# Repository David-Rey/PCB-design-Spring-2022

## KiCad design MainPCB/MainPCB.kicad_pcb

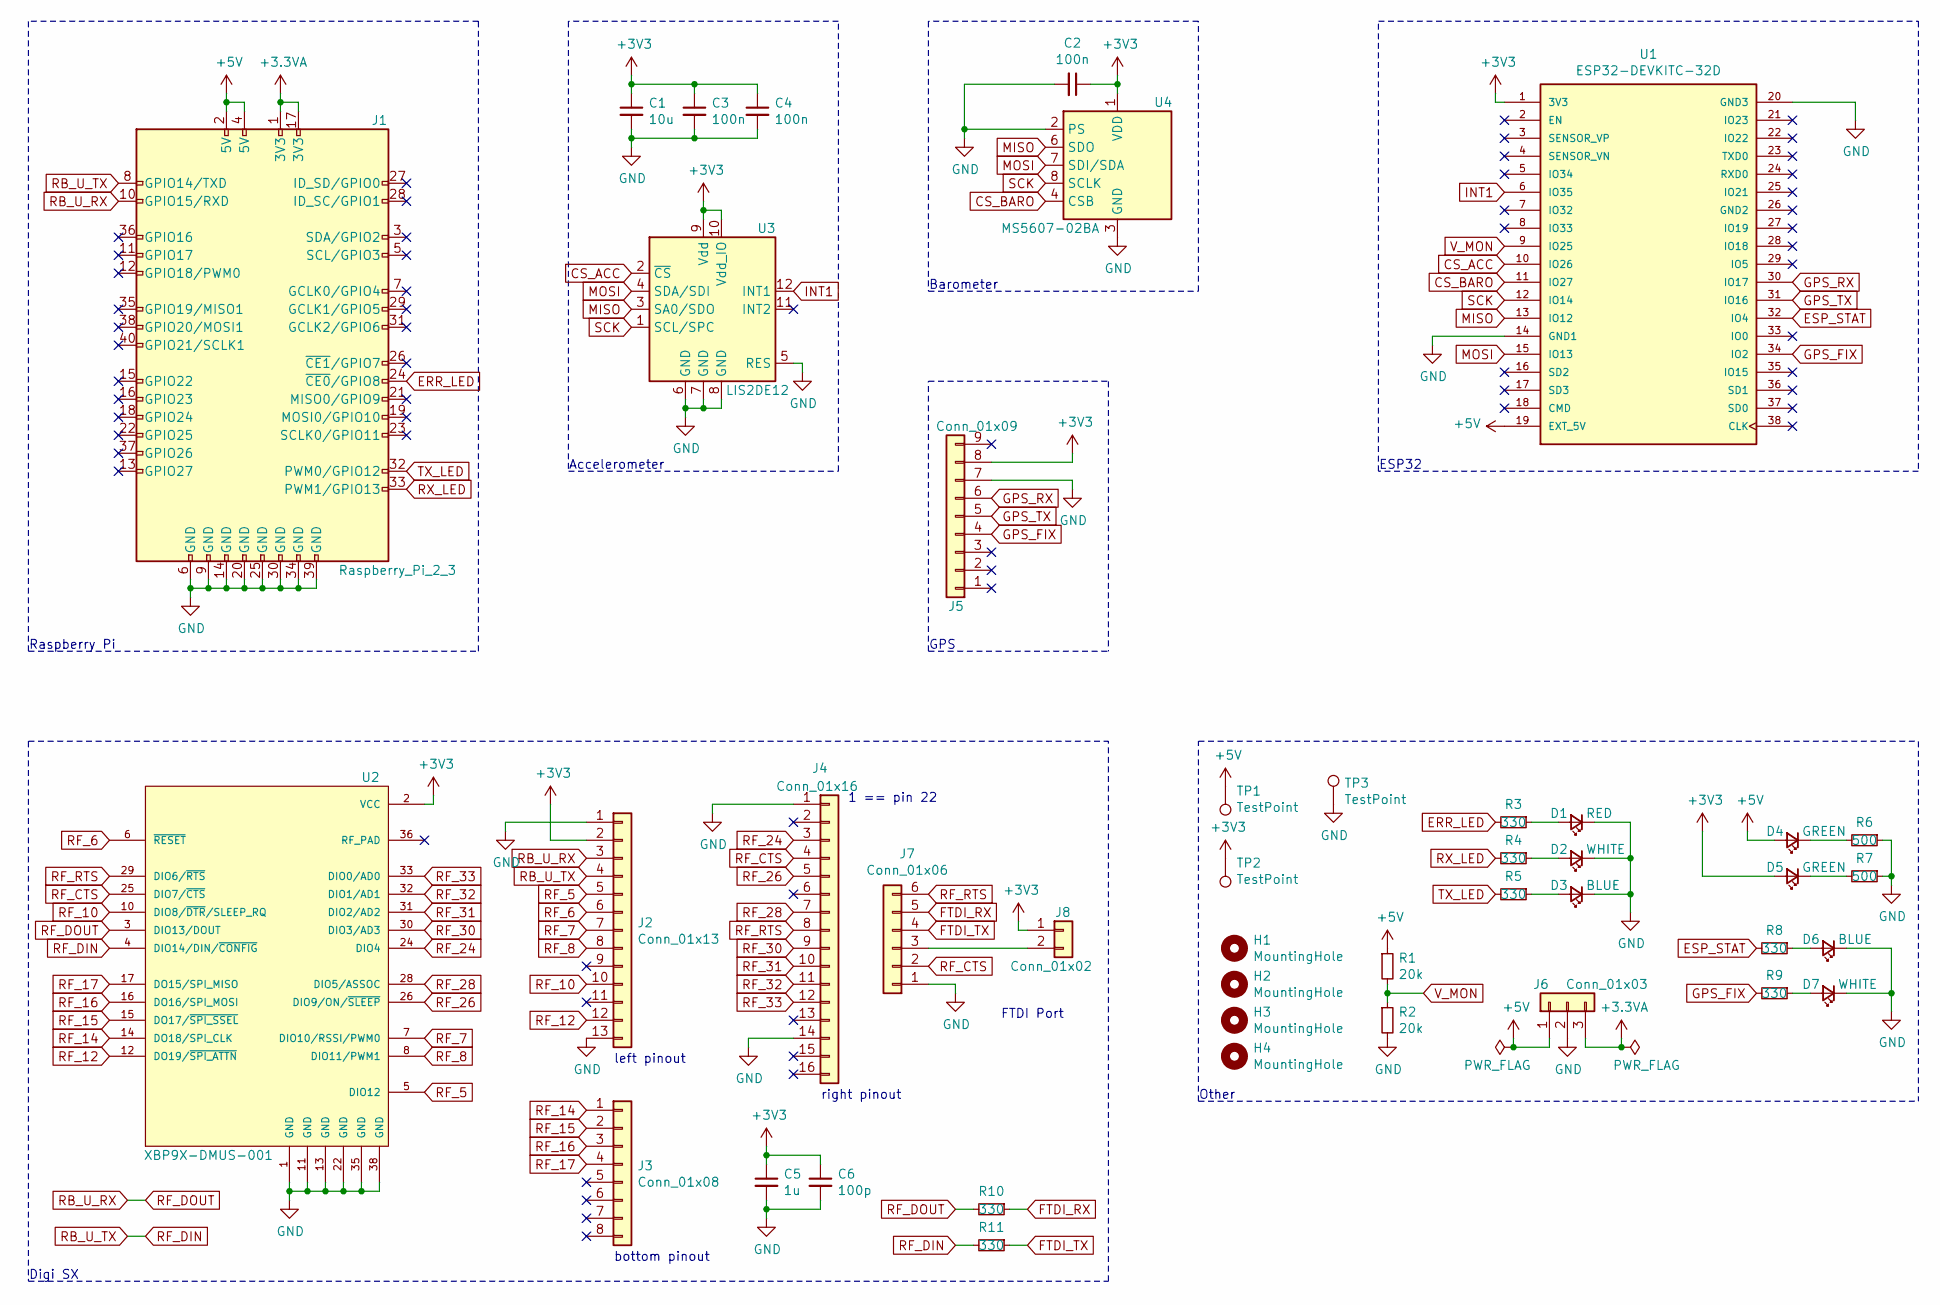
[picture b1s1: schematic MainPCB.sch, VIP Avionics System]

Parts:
C1: 10u; C_0603_1608Metric_Pad1.08x0.95mm_HandSolder
C2, C3, C4: 100n; C_0603_1608Metric_Pad1.08x0.95mm_HandSolder
C5: 1u; C_0603_1608Metric_Pad1.08x0.95mm_HandSolder
C6: 100p; C_0603_1608Metric_Pad1.08x0.95mm_HandSolder
D1: RED; LED_0805_2012Metric_Pad1.15x1.40mm_HandSolder
D2, D7: WHITE; LED_0805_2012Metric_Pad1.15x1.40mm_HandSolder
D3, D6: BLUE; LED_0805_2012Metric_Pad1.15x1.40mm_HandSolder
D4, D5: GREEN; LED_0805_2012Metric_Pad1.15x1.40mm_HandSolder
H1, H2, H3, H4: MountingHole; MountingHole_3mm
J1: Raspberry_Pi_2_3; PinSocket_2x20_P2.54mm_Vertical
J2: Conn_01x13; PinSocket_1x13_P2.54mm_Vertical
J3: Conn_01x08; PinSocket_1x08_P2.54mm_Vertical
J4: Conn_01x16; PinSocket_1x16_P2.54mm_Vertical
J5: Conn_01x09; PinSocket_1x09_P2.54mm_Vertical
J6: Conn_01x03; TerminalBlock_Phoenix_PT-1,5-3-5.0-H_1x03_P5.00mm_Horizontal
J7: Conn_01x06; PinHeader_1x06_P2.54mm_Horizontal
J8: Conn_01x02; PinHeader_1x02_P2.54mm_Vertical
R1, R2: 20k; R_0805_2012Metric_Pad1.20x1.40mm_HandSolder
R3, R4, R5, R8, R9, R10, R11: 330; R_0805_2012Metric_Pad1.20x1.40mm_HandSolder
R6, R7: 500; R_0805_2012Metric_Pad1.20x1.40mm_HandSolder
TP1, TP2, TP3: TestPoint; TestPoint_Pad_D3.0mm
U1: ESP32-DEVKITC-32D; MODULE_ESP32-DEVKITC-32D; PARTREV 4
U2: XBP9X-DMUS-001; XCVR_XBP9X-DMUS-001; PARTREV K
U3: LIS2DE12; LGA-12_2x2mm_P0.5mm
U4: MS5607-02BA; LGA-8_3x5mm_P1.25mm

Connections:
+3.3VA: J1.1 (3V3), J1.17 (3V3), J6.3
+3V3: C1.1, C2.1, C3.1, C4.1, C5.1, C6.1, D5.2 (A), J2.2, J5.8, J8.1, TP2.1, U1.1 (3V3), U2.2 (VCC), U3.9 (Vdd), U3.10 (Vdd_IO), U4.1 (VDD)
+5V: D4.2 (A), J1.2 (5V), J1.4 (5V), J6.1, R1.1, TP1.1, U1.19 (EXT_5V)
CS_ACC: U1.10 (IO26), U3.2 (~CS)
CS_BARO: U1.11 (IO27), U4.4 (CSB), U4.5 (CSB)
ERR_LED: J1.24 (~CE0~/GPIO8), R3.2
ESP_STAT: R8.2, U1.32 (IO4)
FTDI_RX: J7.5, R10.1
FTDI_TX: J7.4, R11.1
GND: C1.2, C2.2, C3.2, C4.2, C5.2, C6.2, D1.1 (K), D2.1 (K), D3.1 (K), D6.1 (K), D7.1 (K), J1.6 (GND), J1.9 (GND), J1.14 (GND), J1.20 (GND), J1.25 (GND), J1.30 (GND), J1.34 (GND), J1.39 (GND), J2.1, J2.13, J4.1, J4.14, J5.7, J6.2, J7.1, R2.2, R6.1, R7.1, TP3.1, U1.14 (GND1), U1.20 (GND3), U2.1 (GND), U2.11 (GND), U2.13 (GND), U2.22 (GND), U2.35 (GND), U2.38 (GND), U3.5 (RES), U3.6 (GND), U3.7 (GND), U3.8 (GND), U4.2 (PS), U4.3 (GND)
GPS_FIX: J5.4, R9.2, U1.34 (IO2)
GPS_RX: J5.6, U1.30 (IO17)
GPS_TX: J5.5, U1.31 (IO16)
INT1: U1.6 (IO35), U3.12 (INT1)
MISO: U1.13 (IO12), U3.3 (SA0/SDO), U4.6 (SDO)
MOSI: U1.15 (IO13), U3.4 (SDA/SDI), U4.7 (SDI/SDA)
unnamed: D1.2 (A), R3.1
unnamed: D2.2 (A), R4.1
unnamed: D3.2 (A), R5.1
unnamed: D4.1 (K), R6.2
unnamed: D5.1 (K), R7.2
unnamed: D6.2 (A), R8.1
unnamed: D7.2 (A), R9.1
unnamed: J7.3, J8.2
RB_U_RX: J1.10 (GPIO15/RXD), J2.3, R10.2, U2.3 (DIO13/DOUT)
RB_U_TX: J1.8 (GPIO14/TXD), J2.4, R11.2, U2.4 (DIO14/DIN/~CONFIG)
RF_5: J2.5, U2.5 (DIO12)
RF_6: J2.6, U2.6 (~RESET)
RF_7: J2.7, U2.7 (DIO10/RSSI/PWM0)
RF_8: J2.8, U2.8 (DIO11/PWM1)
RF_10: J2.10, U2.10 (DIO8/~DTR~/SLEEP_RQ)
RF_12: J2.12, U2.12 (DO19/~SPI_ATTN)
RF_14: J3.1, U2.14 (DO18/SPI_CLK)
RF_15: J3.2, U2.15 (DO17/~SPI_SSEL)
RF_16: J3.3, U2.16 (DO16/SPI_MOSI)
RF_17: J3.4, U2.17 (DO15/SPI_MISO)
RF_24: J4.3, U2.24 (DIO4)
RF_26: J4.5, U2.26 (DIO9/ON/~SLEEP)
RF_28: J4.7, U2.28 (DIO5/ASSOC)
RF_30: J4.9, U2.30 (DIO3/AD3)
RF_31: J4.10, U2.31 (DIO2/AD2)
RF_32: J4.11, U2.32 (DIO1/AD1)
RF_33: J4.12, U2.33 (DIO0/AD0)
RF_CTS: J4.4, J7.2, U2.25 (DIO7/~CTS)
RF_RTS: J4.8, J7.6, U2.29 (DIO6/~RTS)
RX_LED: J1.33 (PWM1/GPIO13), R4.2
SCK: U1.12 (IO14), U3.1 (SCL/SPC), U4.8 (SCLK)
TX_LED: J1.32 (PWM0/GPIO12), R5.2
V_MON: R1.2, R2.1, U1.9 (IO25)

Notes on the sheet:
1 == pin 22
Raspberry Pi
Accelerometer
Barometer
left pinout
bottom pinout
right pinout
Digi SX
FTDI Port
Other
ESP32
GPS

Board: 2 copper layers, 43 parts (0 on the bottom side), 49 nets, no tracks yet.

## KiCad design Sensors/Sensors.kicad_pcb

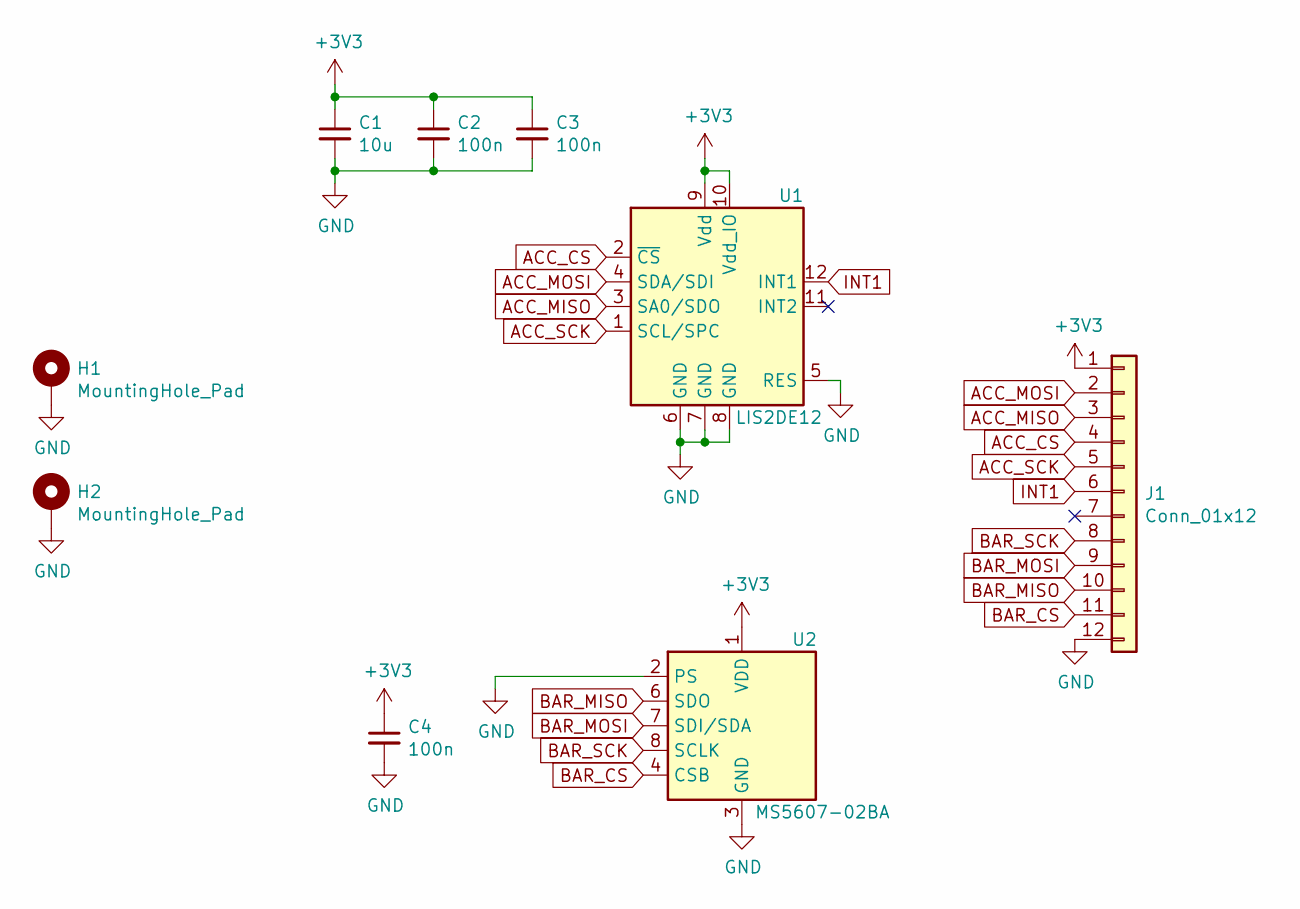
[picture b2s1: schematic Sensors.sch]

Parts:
C1: 10u; C_0603_1608Metric_Pad1.08x0.95mm_HandSolder
C2, C3, C4: 100n; C_0603_1608Metric_Pad1.08x0.95mm_HandSolder
H1, H2: MountingHole_Pad; MountingHole_2.5mm_Pad_Via
J1: Conn_01x12; PinHeader_1x12_P2.54mm_Vertical
U1: LIS2DE12; LGA-12_2x2mm_P0.5mm
U2: MS5607-02BA; LGA-8_3x5mm_P1.25mm

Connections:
+3V3: C1.1, C2.1, C3.1, C4.1, J1.1, U1.9 (Vdd), U1.10 (Vdd_IO), U2.1 (VDD)
ACC_CS: J1.4, U1.2 (~CS)
ACC_MISO: J1.3, U1.3 (SA0/SDO)
ACC_MOSI: J1.2, U1.4 (SDA/SDI)
ACC_SCK: J1.5, U1.1 (SCL/SPC)
BAR_CS: J1.11, U2.4 (CSB), U2.5 (CSB)
BAR_MISO: J1.10, U2.6 (SDO)
BAR_MOSI: J1.9, U2.7 (SDI/SDA)
BAR_SCK: J1.8, U2.8 (SCLK)
GND: C1.2, C2.2, C3.2, C4.2, H1.1, H2.1, J1.12, U1.5 (RES), U1.6 (GND), U1.7 (GND), U1.8 (GND), U2.2 (PS), U2.3 (GND)
INT1: J1.6, U1.12 (INT1)

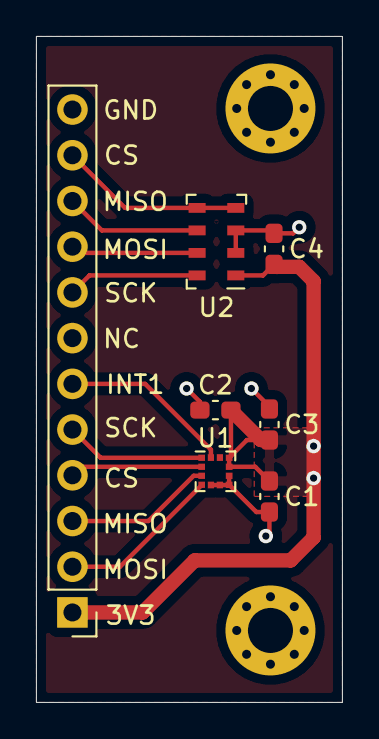
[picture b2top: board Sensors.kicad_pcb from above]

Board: 2 copper layers, 17.0 x 37.0 mm, 9 parts (0 on the bottom side), 11 nets.

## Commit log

2022-02-21 Create test
